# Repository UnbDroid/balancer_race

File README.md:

# Balancing Robot Race - RoboGames 2019

This is the Git repository containing all documents, code and schematics
used in the construction of DROID's robot.

### Cross-Compiling

Available at ```/ccdir```, the ```compile_rasp.sh``` file contains a script for
cross-compiling C code for the Raspberry Pi. It is a much faster process
than compiling code directly at the Raspberry.

Run ```$ sudo apt install gcc-arm-linux-gnueabi``` to install the ARM11 GCC.

All the library files needed must be provided. In this particular case,
we put them all in the same directory as the main code.

### Main Code and Threading

The main code, available at the ```main.c``` file under ```/code```, uses the ```pthread```
wrapper provided by the WiringPi library to parallelize the execution of the
code modules. Reference and documentation available at [WiringPi website](http://www.wiringpi.com).

### Information about DROID-UnB

DROID is a robotic competion team based in the university of Brasília - UnB.

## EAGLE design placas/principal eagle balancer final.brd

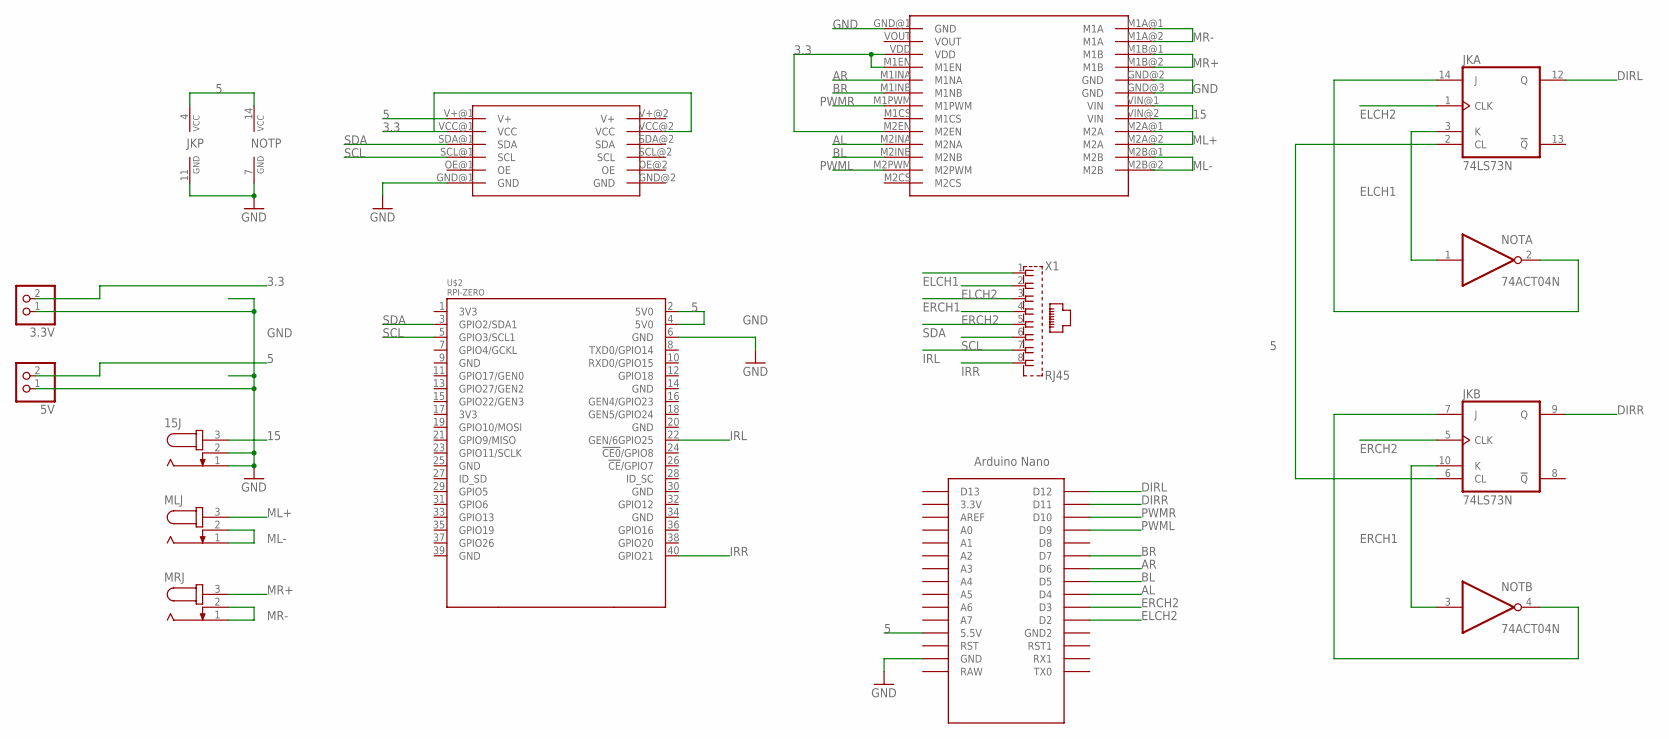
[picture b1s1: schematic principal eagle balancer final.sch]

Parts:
3.3V, 5V: PINHD-1X2; 1X02
15J: JACK-PLUG1; SPC4078
JK: 74LS73N; DIL14
MLJ: JACK-PLUG1; SPC4078
MRJ: JACK-PLUG1; SPC4078
NOT: 74ACT04N; DIL14
U$1: PCA; PCA_P
U$2: RPI-ZERO; RASPBERRYPI_BASTELSTUBE_V13_RASPI_BOARD_B+_FULL
U$3: VNH5019; VNH5019_P
U$4: NANO
X1: RJ45; RJ45_P

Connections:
3.3: 3.3V.2, U$1.VCC@1 (VCC), U$1.VCC@2 (VCC), U$3.M1EN, U$3.M2EN, U$3.VDD
5: 5V.2, JK.2 (CL), JK.4 (VCC), JK.6 (CL), NOT.14 (VCC), U$1.V+@1 (V+), U$2.2 (5V0), U$2.4 (5V0), U$4.5V (5.5V)
15: 15J.3, U$3.VIN@1 (VIN), U$3.VIN@2 (VIN)
AL: U$3.M2INA (M2NA), U$4.D4
AR: U$3.M1INA (M1NA), U$4.D6
BL: U$3.M2INB (M2NB), U$4.D5
BR: U$3.M1INB (M1NB), U$4.D7
DIRL: JK.12 (Q), U$4.D12
DIRR: JK.9 (Q), U$4.D11
ELCH1: JK.3 (K), NOT.1 (I), X1.1
ELCH2: JK.1 (CLK), U$4.D2, X1.2
ERCH1: JK.10 (K), NOT.3 (I), X1.3
ERCH2: JK.5 (CLK), U$4.D3, X1.4
GND: 3.3V.1, 5V.1, 15J.1, 15J.2, JK.11 (GND), NOT.7 (GND), U$1.GND@1 (GND), U$2.6 (GND), U$3.GND@1 (GND), U$3.GND@2 (GND), U$3.GND@3 (GND), U$4.GND
IRL: U$2.22 (GEN/6GPIO25), X1.7
IRR: U$2.40 (GPIO21), X1.8
ML+: MLJ.3, U$3.M2A@1 (M2A), U$3.M2A@2 (M2A)
ML-: MLJ.1, MLJ.2, U$3.M2B@1 (M2B), U$3.M2B@2 (M2B)
MR+: MRJ.3, U$3.M1B@1 (M1B), U$3.M1B@2 (M1B)
MR-: MRJ.1, MRJ.2, U$3.M1A@1 (M1A), U$3.M1A@2 (M1A)
unnamed: JK.14 (J), NOT.2 (O)
unnamed: JK.7 (J), NOT.4 (O)
PWML: U$3.M2PWM, U$4.D9
PWMR: U$3.M1PWM, U$4.D10
SCL: U$1.SCL@1 (SCL), U$2.5 (GPIO3/SCL1), X1.6
SDA: U$1.SDA@1 (SDA), U$2.3 (GPIO2/SDA1), X1.5

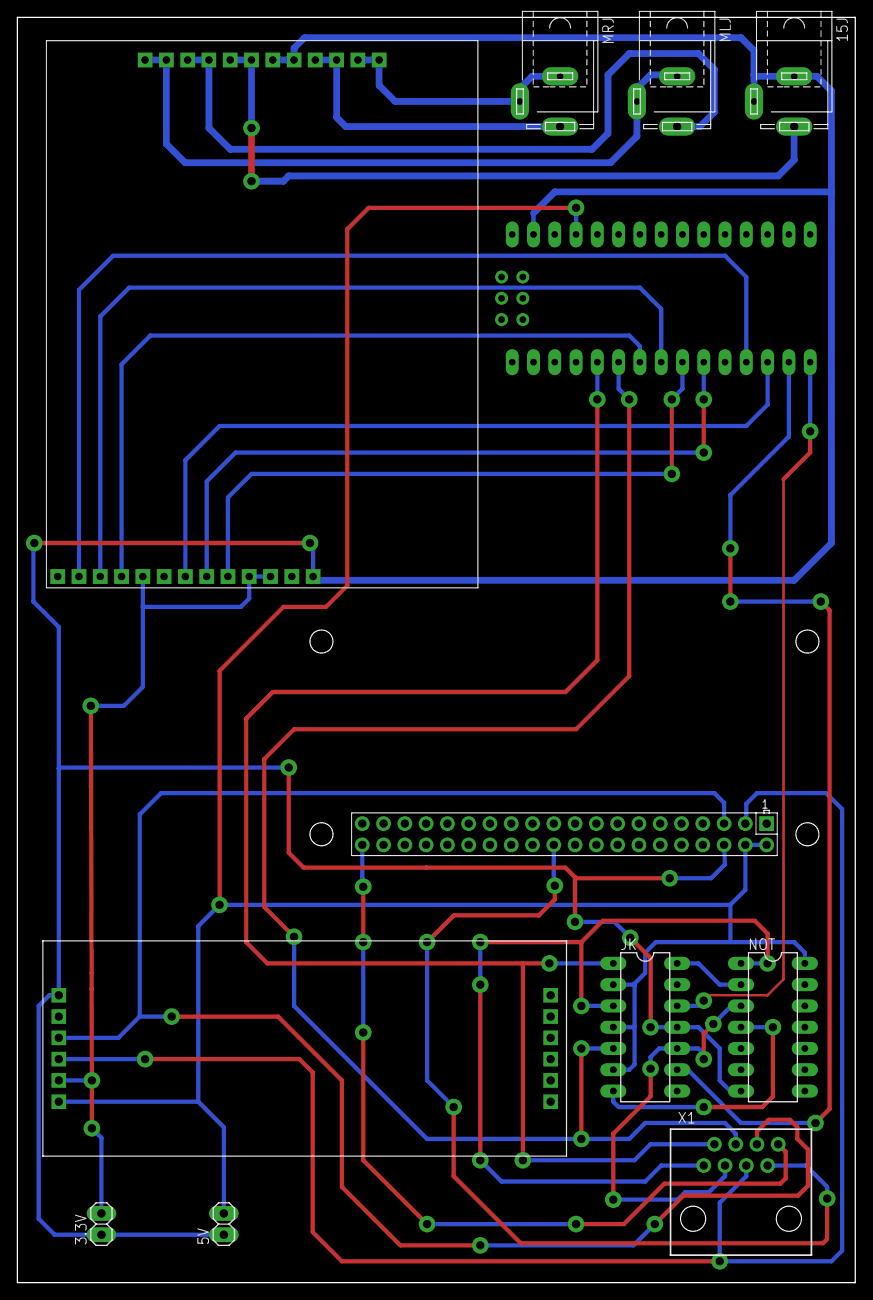
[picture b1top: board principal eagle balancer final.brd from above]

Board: 2 copper layers, 100.0 x 151.0 mm, 12 parts (0 on the bottom side), 26 nets.

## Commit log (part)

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2018-01-14 renomeando algumas pastas
2018-01-15 adiconando os scripts
2018-01-15 suporte ao led
2018-01-15 Beginning to organize the main code
2018-01-16 Added led support to main.c and adapted jstick.c interface with main for ease of maintenance
2018-01-16 Added led.c file with led control support
2018-01-16 Removed main output file which should not be there
2018-01-16 adicionando a placa do painel
2018-01-16 Added yellow color support (no, seriously)
2018-01-16 Added main thread for experimenting with stuff
2018-01-16 Changed the jstick.c interface again
2018-01-16 Now it is compiling
2018-01-16 conexões da placa principal feitas no esquematico
2018-01-17 minor improvements
2018-01-17 projeto da placa do painel finalizado
2018-01-17 pdfs invertidos prontos para impressão corregados no repositório
2018-01-17 pequena correção na placa principal, arvo do fritiging
2018-01-18 pequena correção na placa alimentação, arquivo pdf
2018-01-20 New pin values set after making of PCBs
2018-01-20 Optimized led_color function
2018-01-20 Now compile_rasp.sh removed binary file after transfering file to the Raspberry Pi
2018-01-20 Made minor changes to the way the joystick debug is printed
2018-01-22 Fixed styling of README.md
2018-01-23 Tested and fixed motor driver code and hardware. Working fine.
2018-01-23 Added kill, shutdown and reboot routines through controller. Removed keyboard kill.
2018-01-23 Version 2
    Actualizacion de los reguladores, step down
2018-01-23 pdf placa alimentação2
2018-01-24 Fixed README.md broken link
2018-01-26 corrigindo pequeno erro no codigo do pbservador, que fazia com que o programa não esperece a trade do observador encerrar para fechar
2018-01-26 Changed fechar variable name to close_program
2018-01-26 Began to modify led.c file to support LED states rather than simply colors
2018-01-26 Modified main.c and watcher.c to adapt to the new LED features
2018-01-26 placa dos sensores finalizada
2018-01-26 pdf placa sensores pronto para impressão
2018-01-28 Many new features added, including:
    LED states fully operational.
    LED support completely modified to support LED states.
    SU check not believing the user anymore. Now checking with geteuid() function.
    Encapsulated the end of the main function in a clean_up() function.
2018-01-28 Added debug flag feature and debug screen. Still has some bugs to fix.
2018-01-30 Reversed encoder direction on the right motor
2018-01-30 Added print_message() function for debugging
2018-01-30 Fixed motor bug. For the record: Coast and Brake functions were the source
2018-01-30 Renamed last_update variable as last_led_update to avoid conflict
2018-01-30 Added sensors thread to the main code and began to make sense of IMU data. WIP
2018-01-30 Gyroscope now working, debug screen now contains its data.
2018-01-31 Uncommented accel data prints
2018-01-31 Debug screen is much more complete now
2018-01-31 Now updating IR along with IMU under sensors thread
2018-01-31 Alinhamento de algumas trilhas da placa
2018-02-01 Added routine for testing out motors in the main thread
2018-02-01 Minor changes for testing purposes
2018-02-01 Optimized padding in print_message() function
2018-02-01 Trying to figure out the accelerometer.
2018-02-01 Added more prints using print_message() to try to figure out wtf is happening to the accelerometer.'
2018-02-02 testes para descobrir erro da libmath na compilação cruzada , erro encontrado mas não corrigido ainda
2018-02-02 fazendo o script de compilação voltar a usar o -lm
2018-02-02 Adicionado pasta do compilador que funciona para cross compile. Retirado dos tools fornecido pelo raspberry.
2018-02-02 corrigindo um eror de otimização
2018-02-02 Removed debug prints to clean up the mess caused by the math.h bug
2018-02-02 Added delay to avoid overloading CPU with main_thread
2018-02-02 Removed derivatives to avoid amplification of sensor noise
2018-02-03 Added soft reset on the magnetometer before configuring it
2018-02-03 Corrected mistake. Magnetometer sensitivity is read-only and probably factory-defined
2018-02-03 Added magnetometer angular position calculations.
2018-02-03 Put linear values in magnet angular velocity data temporarily for debug purposes
2018-02-03 Now code prints min and max values while they are generated
2018-02-03 Magnetometer now checks if there is new data before reading it
2018-02-03 Removed data ready check. Apparently not working properly.
2018-02-03 Now calibMag.c prints the definitions for copying and pasting
2018-02-03 Modified start-up routine of the AK8963 magnetometer
2018-02-03 magnetometro e acelerometro funcionando, e tratado para caso em que a posição do robo não pode ser medida
2018-02-04 script de compilação auterado para não precisar digitar a senha toda vez
2018-02-04 arrumando o print
2018-02-04 atualizando para o bruno
2018-02-04 Modified debug screen to adapt to new format of sensors.c structs
2018-02-04 Removed acceleration values from imu structs since they will not be used
2018-02-05 Added support for supervisory system
2018-02-05 adicionando o codigo de teste para o servidor socket
2018-02-05 Removed forgotten printfs that were used for debug purposes
2018-02-05 Fixed supervisory thread not closing, again.
2018-02-05 nao é mais necessario
2018-02-05 criado a pasta do supervisorio com o seu executavel dentro para sistemas x64. codigo fonte também na mesma pasta com extensão .pde
2018-02-07 mudando a porta de comunicação para uma porta menos usada por outros sftwares e serviçõs de rede
2018-02-07 codigo de matlab que recebi dados como cliente soket e plota em um grafico 3D online
2018-02-07 modificando a parte do supervisório para poder comunicar com o matlab também
2018-02-08 Modified sensors thread trying to improve steadiness of the update rate.
2018-02-08 Changed MUITOMAIOR definition name to MUCHBIGGER for language standardizing purposes.
2018-02-08 Added imu.dt to the message sent to the MATLAB client
2018-02-08 Added comments to the led.c file
2018-02-08 Added more comments to the led.c file
2018-02-08 alterando o enviu do matlab para angulo ou envez de leitura direto dos eixos
2018-02-09 erro de compilação
2018-02-09 Finished commenting all main parts of the led.c file
2018-02-09 Renamed supervisorio folder to supervisory for language standardizing purposes
2018-02-13 Set accelerometer and gyroscope sample rate to 100Hz to match magnetometer sample rate. (was 200Hz before)
2018-02-14 mudando para graus a visualisação das atitudes
2018-02-14 deletado pelo motivo do cmommit anterior
2018-02-14 Changed yaw-pitch-roll calculations
2018-02-14 codigo para fazer o triad no matlab
2018-02-15 agora não realiza a etapa de correção do filtro de kalman caso os valores recebido da TRIAD sejam todos iguais a leitura anterior
2018-02-15 acelerometro ignorado caso seu módulo seja 1.3x aceleração da gravidade
2018-02-15 agora somente o filtro e tela redimencionavel
2018-02-15 mudanças no supervisório do matlab e regulagens de parametro do filtro de kalman
2018-02-15 brincando de controle
2018-02-15 corrigindo a comunicação com o processing
2018-02-16 corrição de erro na comunicação do supervisório
2018-02-16 Forgot to set accelerometer to 2g scale, the same used in the main program, before calibrating.
2018-02-20 modificações para deixar a comunicação mais roposta, ainda falta fazer na parte de matlab também e modificar algumas coisas no código em java, mas já esta funcionando melhor do que antes
2018-02-20 mudança de algumas constantes, mudança do tratamento de ruidos do acelerometro
2018-02-25 Now treating accel bias. Calibration still not 100% but working way better now.
2018-02-25 Added calibTriad.c file for calibration of the navigational system vectors of the TRIAD algorithm.
    Calibration should work fine with just the triad.calib binary file but the program generates a txt file for backup.
2018-02-25 again
2018-02-26 correção de alguns erros no controlador e no filtro de kalman da main
2018-02-26 Now START+SELECT ends the program, instead of calling the watcher while START+SELECT+LEFT calls the watcher.
2018-02-26 Added plot data for accelerometer independent axis measurements with and without the motor running
2018-02-26 gráficos dos valores de aceleração de cada eixo sem filtrar
2018-02-26 Improved plot infrastructure
2018-02-27 Added median filtering to the accelerometer readings, hoping it will eliminate the accel vibrations.
2018-02-27 Added a script for speeding up plotting data
2018-02-27 Activated accelerometer's internal DLPF (Differential Low-Pass Filter).
2018-02-28 ajustado a largura da banda do filtro do acelerômetro
2018-02-28 Fixed debug screen bug where IMU Time value was printed wrong.
2018-03-02 dados
2018-03-02 Fixed magnetometer reading routine.
    Now the code checks for magnetometer DRDY bit to see if there is new data.
2018-03-03 arrumando a condição de zerar o integrador
2018-03-03 midificando a main para testar os encoders
2018-03-03 novos dados e gráficos
2018-03-03 Added Encoder data for plotting
2018-03-04 corrigindo o script do fastplot do matlab
2018-03-05 Changed the way motor speed is measured. Much better now.
2018-03-05 Added motor speed control
2018-03-06 regulando contrle de angulo para novos valores de velocidade dos motores
2018-03-07 Made changes to the motor control architecture (same results though)
2018-03-08 implementação do controle PID para contnrole do motor pelo arduino e adaptação do controle da letícia para o arduino nano
2018-03-10 almentamos a frequencia do arduino, implementamos o controle bang bang para baixas velocidade. PS: as caixas de reduções dos motores estão diferentes, poha miguel!
2018-03-10 Renamed Controel_velocidade to controle_velocidade
2018-03-14 Finished code for communication between Arduino and Raspberry Pi. Still needs some testing when we have the circuit board ready
2018-03-17 tried to make comm work to no avail
2018-03-20 Testes com USB Arduino
    Códigos feitos para criar e testar comunicação USB com o Arduino
2018-03-21 Concluido criação das funções de comunicação com o Arduino.
    funções send_to_arduino e receive_from_arduino criadas. Atualmente esta configurado para suportar até 5 mensagens de 20 caracteres.
2018-03-22 added reset timeout for the arduino to avoid integrator windup
    it also helps debugging comm
    built-in led lights up when timeout is reached and turns off when the arduino receives a serial message
2018-03-24 Correção 2 erros
    um que fazia o motor começar a se mexer caso o encoder desse um unico pulso
    e outro erro que fazia com que o integrador do PID acumulasse erro mesmo quando o controle celecionando era o bang bang
2018-03-30 Codigo de testes Serial v3!
    3ª versão dos codigos feitos por mim para testar a comunicação serial. Os dois arquivos estão o mais organizado e comentado que deu. O baudrate foi deixado em 2000000 bps.
2018-03-31 Little code corrections and changes
2018-04-01 Comm+control on the main.c and motor.c
2018-04-06 Controle de 3 níveis emplementado e funcionando!
    funciona com imput do joystick.
2018-04-10 Atualização das placas
    Foram feitas atualizações das de tres tipos de placas
2018-04-10 Library and final PCB
    Atualizaçao e versao final do projeto da placa PCB principal
2018-04-11 began to implement safety stop
    new led state called HALT
    needs testing with the robot
2018-04-13 fixed bug where plotting would cause watcher not to be called
2018-04-16 Versão final placa principal
    Corrigidas as trilhas que levan a tensão de 3.3 a 5V nos CI 7473 e 7404
2018-04-20 safety stop through LT/RT buttons is working
    yay
2018-04-21 Isso... funciona?...
2018-04-22 isso... funciona ainda melhor?...
2018-04-23 Versão 2.0.0. Funciona e esta com todos calibrados.
2018-04-24 Melhorias no controlador de velocidade do robô
2018-04-27 minor changes to the LED behavior
2018-04-28 Versão com reset do integrador depois da scurve.
